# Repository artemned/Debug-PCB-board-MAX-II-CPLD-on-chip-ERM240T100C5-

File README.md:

# Debug-PCB-board-MAX-II-CPLD-on-chip-ERM240T100C5-
##  Some variation board models   

### To create this project I was inspired by the ability to synthesize digital circuits using the Verilog and System Verilog languages.From my own experience, I would like to note that many industrial controllers or programmable relays use “Functional block diagram” semantics as a description of control system algorithms. Naturally, the experience gained with this board can be easily used in industry to obtain reliable, efficient and inexpensive solutions.But and not only in industry.Further in this repository in the Examples package, examples of synthesized circuits will appear. The whole project: entirely built on enthusiasm. Therefore, you can become a co-author and contribute.I am grateful to everyone who has read this far. For questions and suggestions, write to the email address: daineko.a32@mail.ru P.S. All goodness and fresh cookies!

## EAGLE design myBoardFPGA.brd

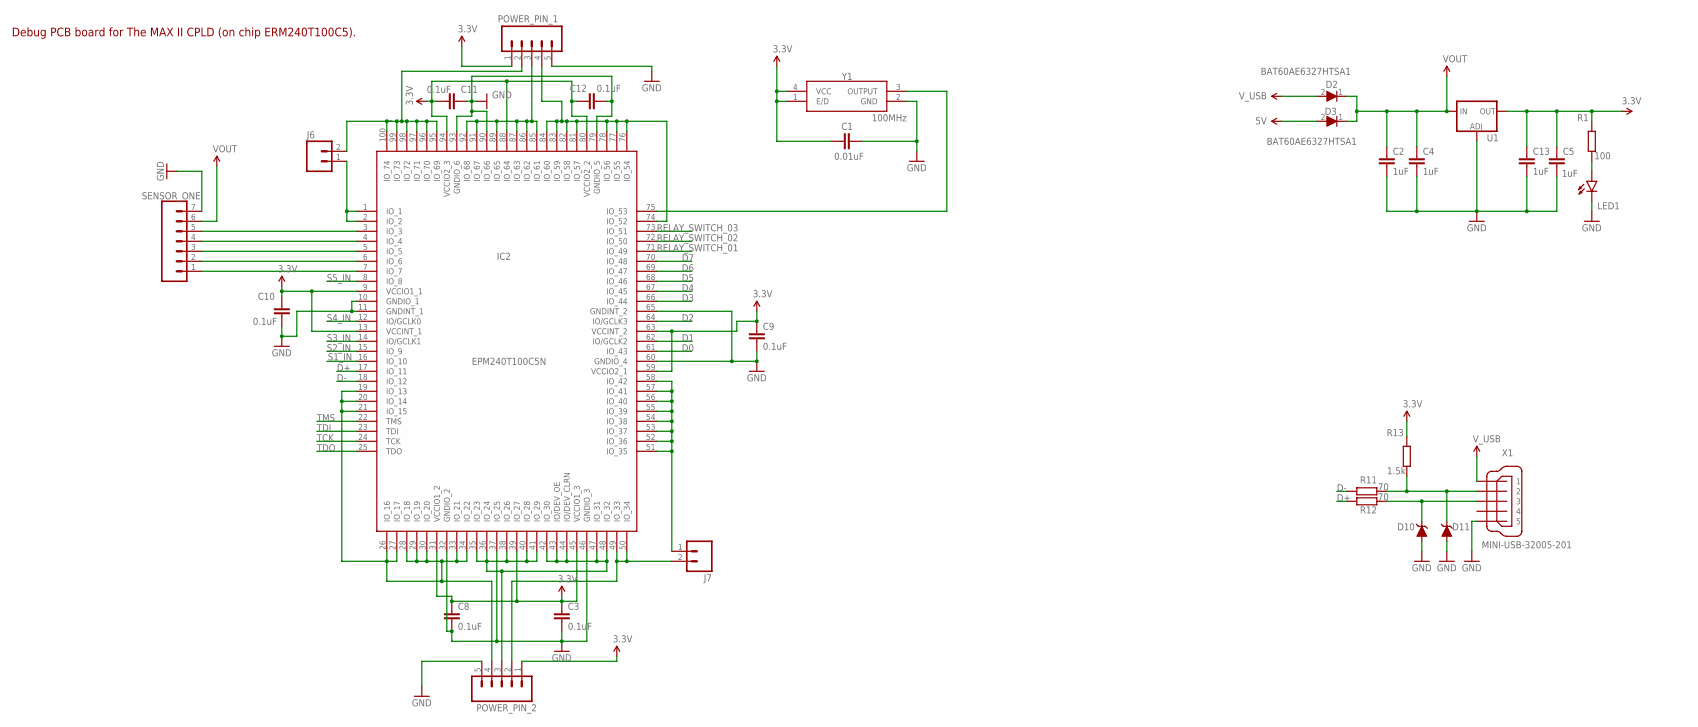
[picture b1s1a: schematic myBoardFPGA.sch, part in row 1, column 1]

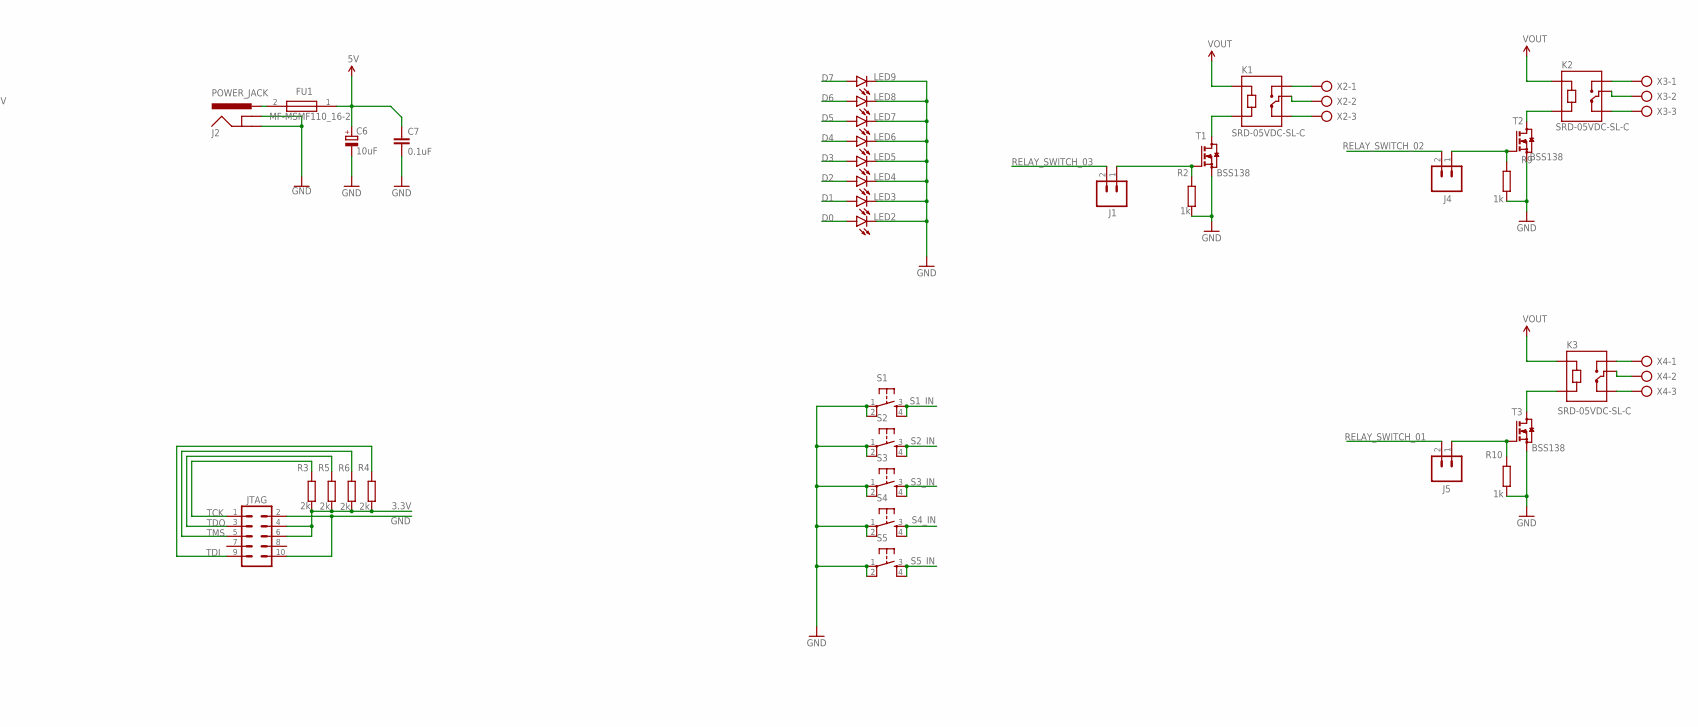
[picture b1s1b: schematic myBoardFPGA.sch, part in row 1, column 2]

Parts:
C1: 0.01uF; C1206
C2, C4, C5, C13: 1uF; C1206
C3, C7, C8, C9, C10, C11, C12: 0.1uF; C1206
C6: 10uF; E2-5
D2, D3: BAT60AE6327HTSA1; SOD2513X110N
D10: 3.3V; BZV55C3V9TP
D11: 3.6; BZV55C3V9TP
FU1: MF-MSMF110_16-2; FUSC4632X85N
IC2: EPM240T100C5N; QFP50P1600X1600X120-100N
J1, J4, J5, J6, J7: M02LOCK; 1X02_LOCK
J2: POWER_JACK; POWER_JACK_PTH
JTAG: M05X2NO_SILK; 2X5_NOSILK
K1, K2, K3: SRD-05VDC-SL-C; RELAY_SRD-05VDC-SL-C
LED1: LEDSML0805; SML0805
LED2, LED3, LED4, LED5, LED6, LED7, LED8, LED9: LEDSMT1206; 1206
POWER_PIN_1, POWER_PIN_2: M05LOCK; 1X05_LOCK
R1: 100; R1206
R2, R9, R10: 1k; R1206
R3, R4, R5, R6: 2k; R1206
R11, R12: 70; R1206
R13: 1.5k; R1206
S1, S2, S3, S4, S5: TAC_SWITCHPTH; TACTILE-PTH
SENSOR_ONE: CONN_07; 1X07
T1, T2, T3: BSS123; SOT23
U1: V_REG_LM1117SOT223; SOT223
X1: MINI-USB-32005-201; 32005-201
X2, X3, X4: AK300/3
Y1: 100MHz; CO4605100000TTR

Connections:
3.3V: C1.1, C3.1, C5.1, C8.1, C9.1, C10.1, C11.2, C12.1, C13.1, IC2.9 (VCCIO1_1), IC2.13 (VCCINT_1), IC2.31 (VCCIO1_2), IC2.39 (IO_27), IC2.45 (VCCIO1_3), IC2.59 (VCCIO2_1), IC2.63 (VCCINT_2), IC2.80 (VCCIO2_2), IC2.88 (IO_64), IC2.94 (VCCIO2_3), JTAG.4, JTAG.6, POWER_PIN_1.1, POWER_PIN_2.1, R1.2, R3.1, R4.1, R5.1, R6.1, R13.2, U1.2 (OUT), U1.4 (OUT), Y1.1 (E/D), Y1.4 (VCC)
5V: C6.+, C7.1, D3.2 (A), FU1.1
D0: IC2.61 (IO_43), LED2.A
D1: IC2.62 (IO/GCLK2), LED3.A
D2: IC2.64 (IO/GCLK3), LED4.A
D3: IC2.66 (IO_44), LED5.A
D4: IC2.67 (IO_45), LED6.A
D5: IC2.68 (IO_46), LED7.A
D6: IC2.69 (IO_47), LED8.A
D7: IC2.70 (IO_48), LED9.A
D+: IC2.17 (IO_11), R12.2
D-: IC2.18 (IO_12), R11.2
GND: C1.2, C2.2, C3.2, C4.2, C5.2, C6.-, C7.2, C8.2, C9.2, C10.2, C11.1, C12.2, C13.2, D10.1 (A), D11.1 (A), IC2.10 (GNDIO_1), IC2.11 (GNDINT_1), IC2.32 (GNDIO_2), IC2.37 (IO_25), IC2.46 (GNDIO_3), IC2.60 (GNDIO_4), IC2.65 (GNDINT_2), IC2.79 (GNDIO_5), IC2.90 (IO_66), IC2.93 (GNDIO_6), J2.GND, J2.GNDBREAK, JTAG.2, JTAG.10, LED1.C, LED2.C, LED3.C, LED4.C, LED5.C, LED6.C, LED7.C, LED8.C, LED9.C, POWER_PIN_1.5, POWER_PIN_2.5, R2.1, R9.1, R10.1, S1.1, S1.2, S2.1, S2.2, S3.1, S3.2, S4.1, S4.2, S5.1, S5.2, SENSOR_ONE.7, T1.2 (S), T2.2 (S), T3.2 (S), U1.1 (ADJ), X1.5, Y1.2 (GND)
unnamed: K1.A2, T1.3 (D)
unnamed: LED1.A, R1.1
unnamed: K1.NO, X2.1
unnamed: K1.NC, X2.3
unnamed: K2.A2, T2.3 (D)
unnamed: J1.1, R2.2, T1.1 (G)
unnamed: K3.A2, T3.3 (D)
unnamed: J4.1, R9.2, T2.1 (G)
unnamed: J5.1, R10.2, T3.1 (G)
unnamed: K1.COM, X2.2
unnamed: K2.NO, X3.1
unnamed: K2.COM, X3.2
unnamed: K2.NC, X3.3
unnamed: K3.COM, X4.2
unnamed: K3.NO, X4.1
unnamed: K3.NC, X4.3
unnamed: IC2.35 (IO_23), IC2.36 (IO_24), IC2.38 (IO_26), IC2.40 (IO_28), IC2.41 (IO_29), IC2.42 (IO_30), IC2.43 (IO/DEV_OE), IC2.44 (IO/DEV_CLRN), IC2.47 (IO_31), IC2.48 (IO_32), POWER_PIN_2.3
unnamed: IC2.19 (IO_13), IC2.20 (IO_14), IC2.21 (IO_15), IC2.26 (IO_16), IC2.27 (IO_17), IC2.28 (IO_18), IC2.29 (IO_19), IC2.30 (IO_20), IC2.33 (IO_21), IC2.34 (IO_22), POWER_PIN_2.4
unnamed: D11.2 (C), R11.1, R13.1, X1.2
unnamed: D10.2 (C), R12.1, X1.3
unnamed: IC2.7 (IO_7), SENSOR_ONE.1
unnamed: IC2.49 (IO_33), IC2.50 (IO_34), J7.2, POWER_PIN_2.2
unnamed: IC2.6 (IO_6), SENSOR_ONE.2
unnamed: IC2.5 (IO_5), SENSOR_ONE.3
unnamed: IC2.51 (IO_35), IC2.52 (IO_36), IC2.53 (IO_37), IC2.54 (IO_38), IC2.55 (IO_39), IC2.56 (IO_40), IC2.57 (IO_41), IC2.58 (IO_42), J7.1
unnamed: IC2.75 (IO_53), Y1.3 (OUTPUT)
unnamed: IC2.4 (IO_4), SENSOR_ONE.4
unnamed: IC2.3 (IO_3), SENSOR_ONE.5
unnamed: IC2.1 (IO_1), IC2.2 (IO_2), J6.1
unnamed: IC2.95 (IO_69), IC2.96 (IO_70), IC2.97 (IO_71), IC2.98 (IO_72), IC2.99 (IO_73), IC2.100 (IO_74), J6.2, POWER_PIN_1.2
unnamed: FU1.2, J2.PWR
unnamed: IC2.74 (IO_52), IC2.76 (IO_54), IC2.77 (IO_55), IC2.78 (IO_56), IC2.81 (IO_57), IC2.82 (IO_58), IC2.83 (IO_59), IC2.84 (IO_60), POWER_PIN_1.4
unnamed: IC2.85 (IO_61), IC2.86 (IO_62), IC2.87 (IO_63), IC2.89 (IO_65), IC2.91 (IO_67), IC2.92 (IO_68), POWER_PIN_1.3
RELAY_SWITCH_01: IC2.71 (IO_49), J5.2
RELAY_SWITCH_02: IC2.72 (IO_50), J4.2
RELAY_SWITCH_03: IC2.73 (IO_51), J1.2
S1_IN: IC2.16 (IO_10), S1.3, S1.4
S2_IN: IC2.15 (IO_9), S2.3, S2.4
S3_IN: IC2.14 (IO/GCLK1), S3.3, S3.4
S4_IN: IC2.12 (IO/GCLK0), S4.3, S4.4
S5_IN: IC2.8 (IO_8), S5.3, S5.4
TCK: IC2.24 (TCK), JTAG.1, R3.2
TDI: IC2.23 (TDI), JTAG.9, R4.2
TDO: IC2.25 (TDO), JTAG.3, R5.2
TMS: IC2.22 (TMS), JTAG.5, R6.2
VOUT: C2.1, C4.1, D2.1 (K), D3.1 (K), K1.A1, K2.A1, K3.A1, SENSOR_ONE.6, U1.3 (IN)
V_USB: D2.2 (A), X1.1

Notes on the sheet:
Debug PCB board for The MAX II CPLD (on chip ERM240T100C5).

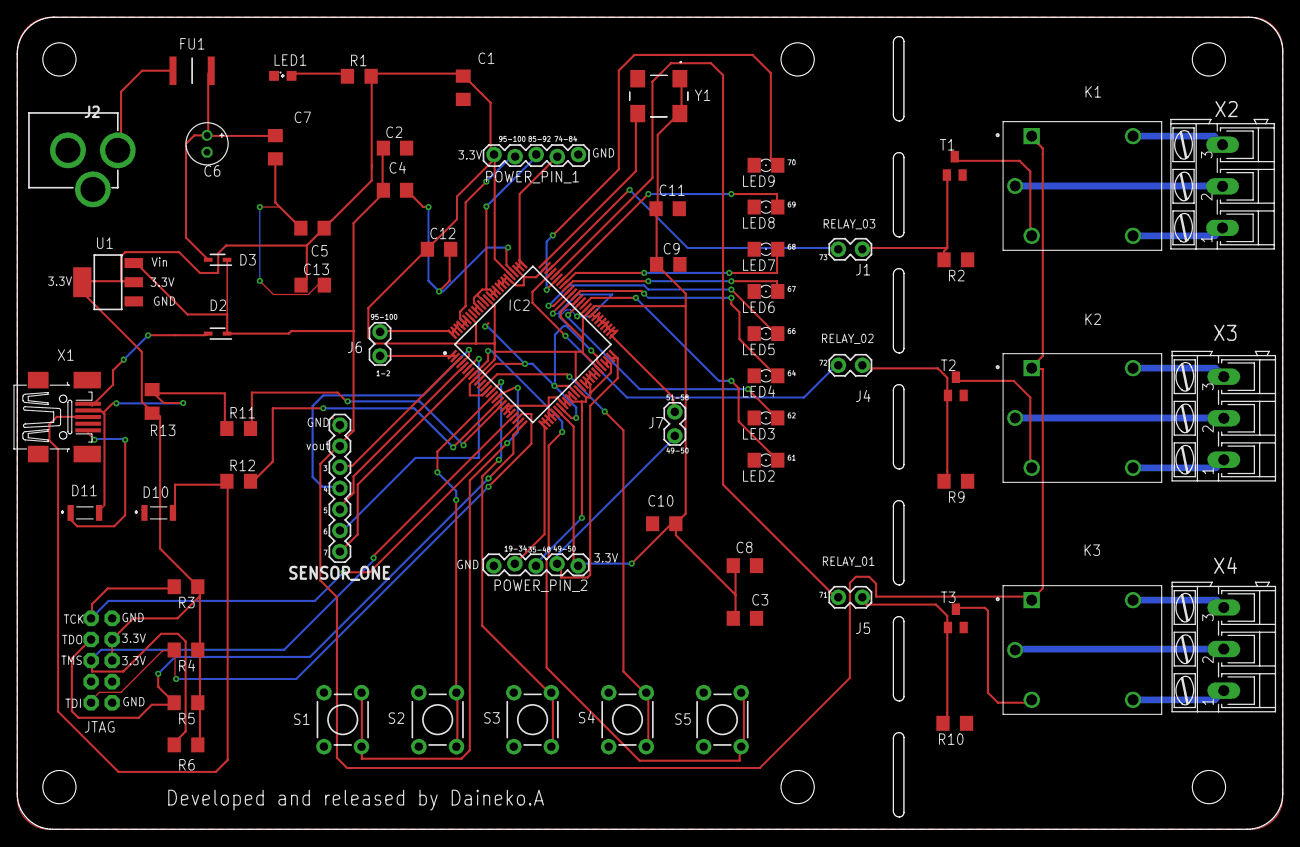
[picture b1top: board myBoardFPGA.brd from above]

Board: 2 copper layers, 152.4 x 97.8 mm, 66 parts (0 on the bottom side), 60 nets.

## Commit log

2020-12-04 Create Example programms
2020-12-16 Update pins

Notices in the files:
parts and their libraries:
SparkFun-Connectors: Licensing: Creative Commons ShareAlike 4.0 International - https://creativecommons.org/licenses/by-sa/4.0
